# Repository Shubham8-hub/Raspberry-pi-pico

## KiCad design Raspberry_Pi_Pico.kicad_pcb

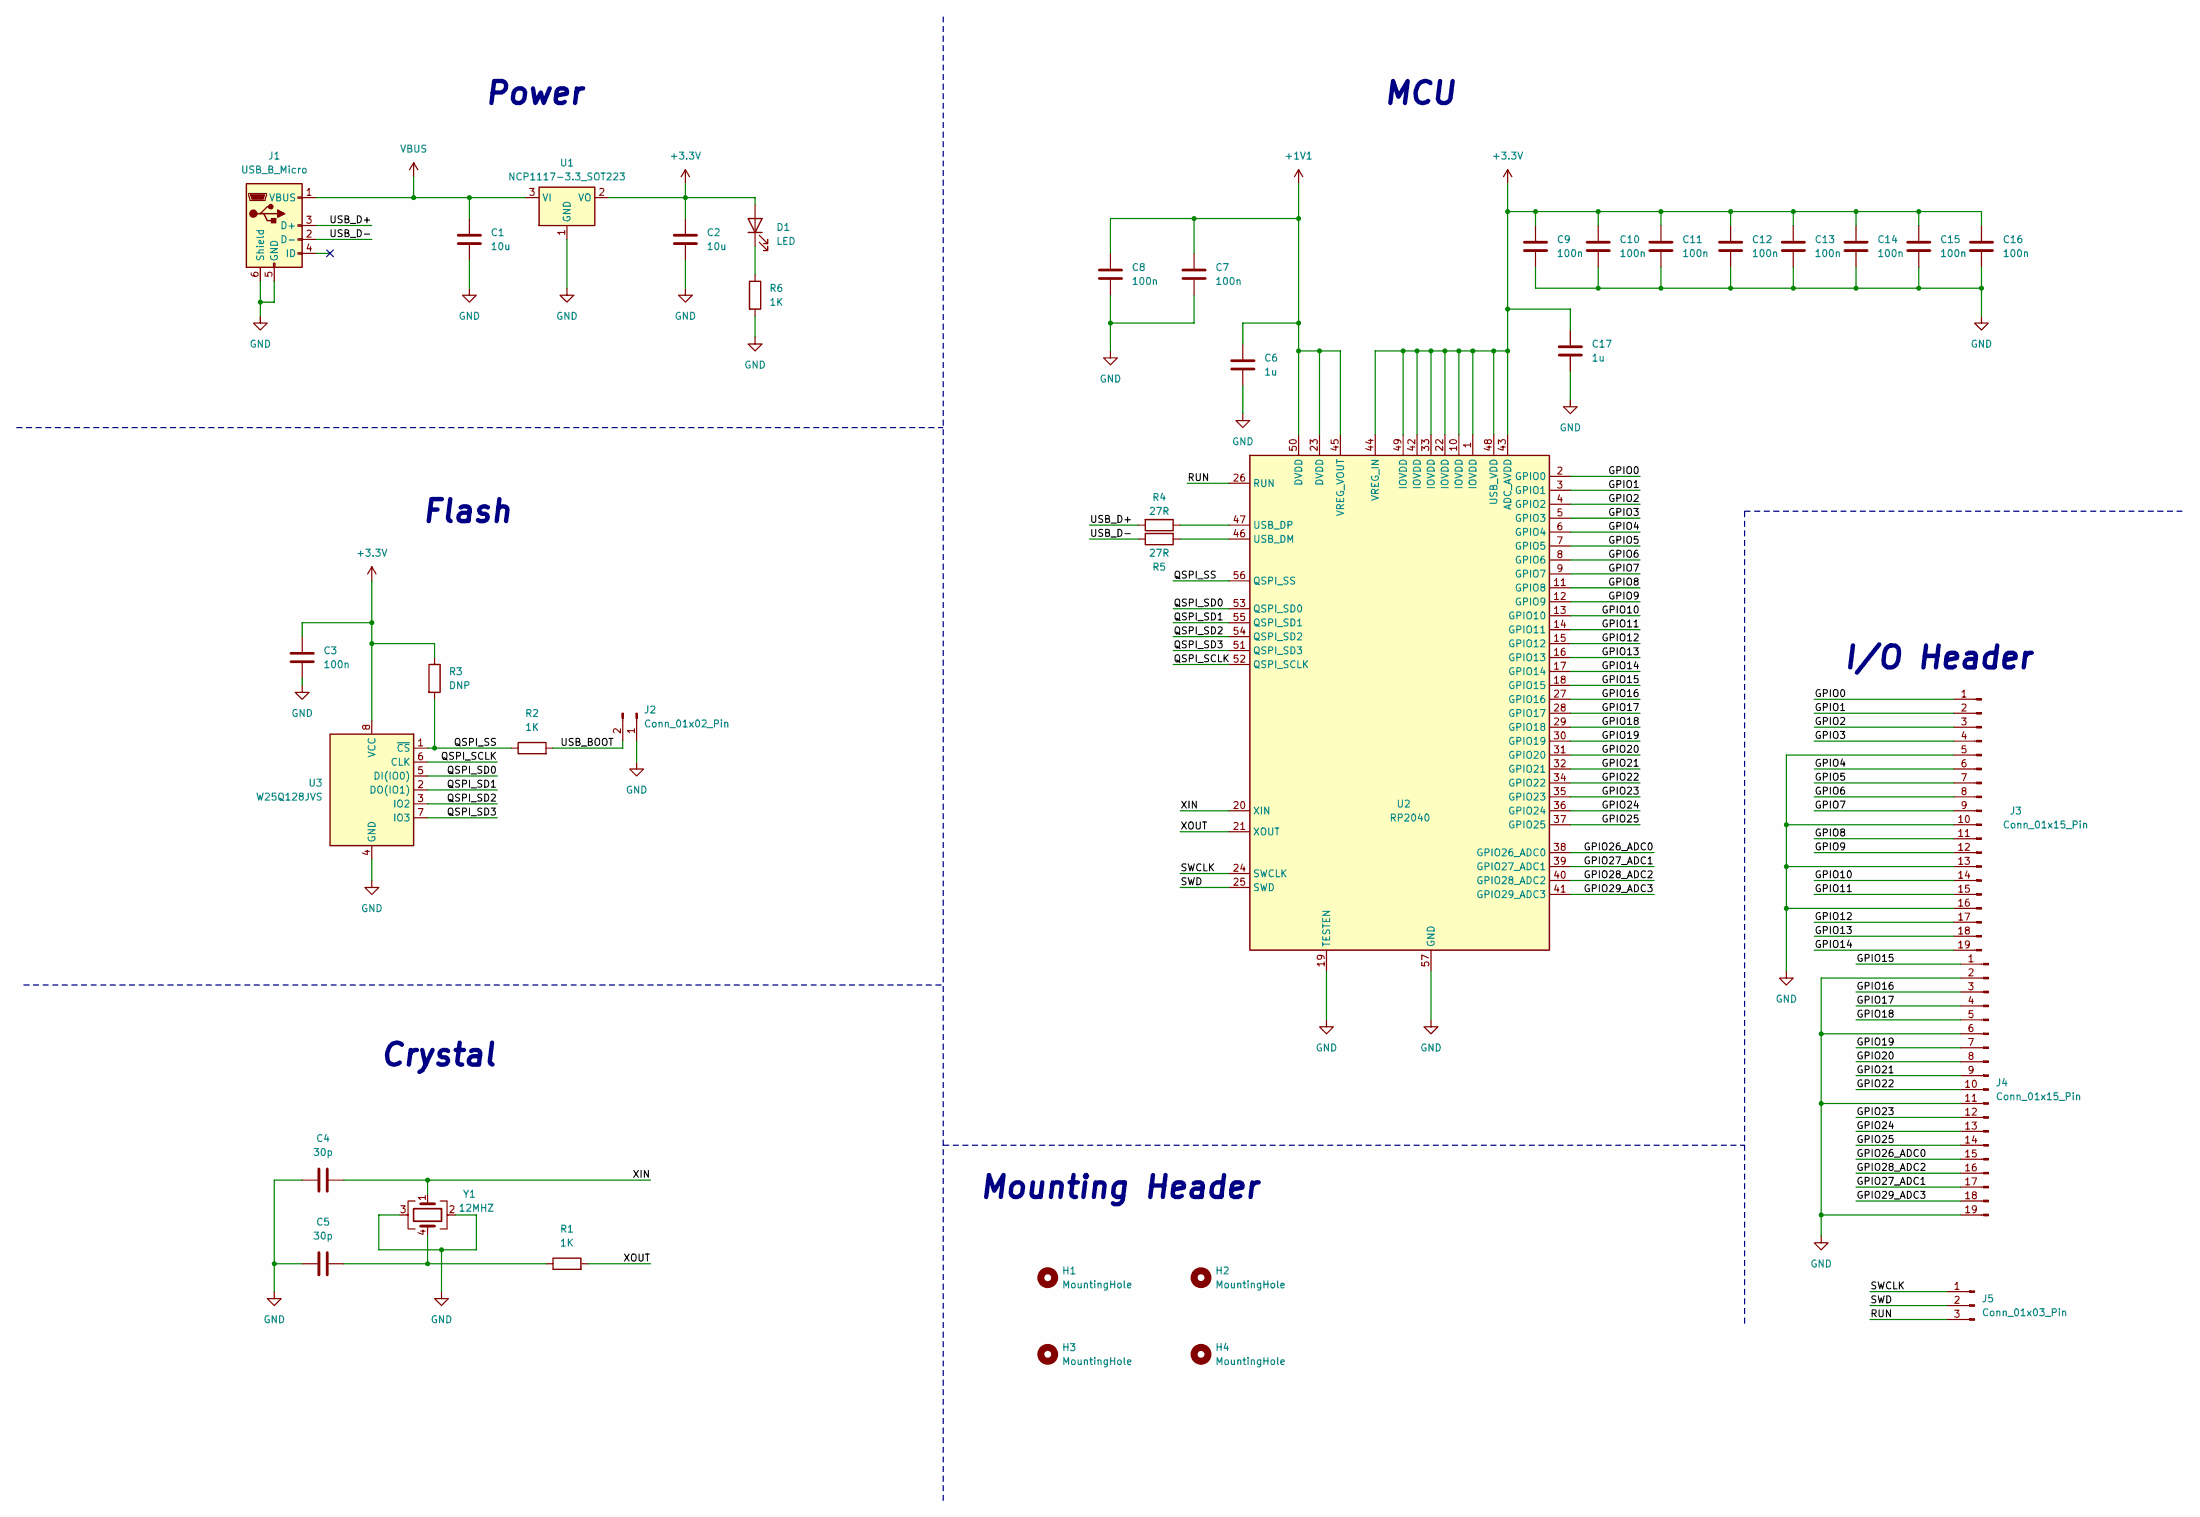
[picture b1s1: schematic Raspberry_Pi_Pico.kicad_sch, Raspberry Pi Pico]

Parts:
C1, C2: 10u; C_0805_2012Metric_Pad1.18x1.45mm_HandSolder
C3, C7, C8, C9, C10, C11, C12, C13, C14, C15, C16: 100n; C_0805_2012Metric_Pad1.18x1.45mm_HandSolder
C4, C5: 30p; C_0805_2012Metric_Pad1.18x1.45mm_HandSolder
C6, C17: 1u; C_0805_2012Metric_Pad1.18x1.45mm_HandSolder
D1: LED; LED_0805_2012Metric
H1, H2, H3, H4: MountingHole; MountingHole_3.2mm_M3_DIN965
J1: USB_B_Micro; USB_Micro-B_Wuerth_629105150521_CircularHoles
J2: Conn_01x02_Pin; PinHeader_1x02_P2.54mm_Vertical
J3, J4: Conn_01x15_Pin; PinHeader_1x19_P2.54mm_Vertical
J5: Conn_01x03_Pin; PinHeader_1x03_P2.54mm_Vertical
R1, R2, R6: 1K; R_0805_2012Metric_Pad1.20x1.40mm_HandSolder
R3: DNP; R_0805_2012Metric_Pad1.20x1.40mm_HandSolder
R4, R5: 27R; R_0805_2012Metric_Pad1.20x1.40mm_HandSolder
U1: NCP1117-3.3_SOT223; SOT-223-3_TabPin2
U2: RP2040; QFN-56-1EP_7x7mm_P0.4mm_EP3.2x3.2mm
U3: W25Q128JVS; SOIC-8_5.23x5.23mm_P1.27mm
Y1: 12MHZ; Crystal_SMD_7050-4Pin_7.0x5.0mm

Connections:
+1V1: C6.1, C7.1, C8.1, U2.23 (DVDD), U2.45 (VREG_VOUT), U2.50 (DVDD)
+3.3V: C2.1, C3.1, C9.1, C10.1, C11.1, C12.1, C13.1, C14.1, C15.1, C16.1, C17.1, D1.2 (A), R3.1, U1.2 (VO), U2.1 (IOVDD), U2.10 (IOVDD), U2.22 (IOVDD), U2.33 (IOVDD), U2.42 (IOVDD), U2.43 (ADC_AVDD), U2.44 (VREG_IN), U2.48 (USB_VDD), U2.49 (IOVDD), U3.8 (VCC)
/GPIO0: J3.1, U2.2 (GPIO0)
/GPIO1: J3.2, U2.3 (GPIO1)
/GPIO2: J3.3, U2.4 (GPIO2)
/GPIO3: J3.4, U2.5 (GPIO3)
/GPIO4: J3.6, U2.6 (GPIO4)
/GPIO5: J3.7, U2.7 (GPIO5)
/GPIO6: J3.8, U2.8 (GPIO6)
/GPIO7: J3.9, U2.9 (GPIO7)
/GPIO8: J3.11, U2.11 (GPIO8)
/GPIO9: J3.12, U2.12 (GPIO9)
/GPIO10: J3.14, U2.13 (GPIO10)
/GPIO11: J3.15, U2.14 (GPIO11)
/GPIO12: J3.17, U2.15 (GPIO12)
/GPIO13: J3.18, U2.16 (GPIO13)
/GPIO14: J3.19, U2.17 (GPIO14)
/GPIO15: J4.1, U2.18 (GPIO15)
/GPIO16: J4.3, U2.27 (GPIO16)
/GPIO17: J4.4, U2.28 (GPIO17)
/GPIO18: J4.5, U2.29 (GPIO18)
/GPIO19: J4.7, U2.30 (GPIO19)
/GPIO20: J4.8, U2.31 (GPIO20)
/GPIO21: J4.9, U2.32 (GPIO21)
/GPIO22: J4.10, U2.34 (GPIO22)
/GPIO23: J4.12, U2.35 (GPIO23)
/GPIO24: J4.13, U2.36 (GPIO24)
/GPIO25: J4.14, U2.37 (GPIO25)
/GPIO26_ADC0: J4.15, U2.38 (GPIO26_ADC0)
/GPIO27_ADC1: J4.17, U2.39 (GPIO27_ADC1)
/GPIO28_ADC2: J4.16, U2.40 (GPIO28_ADC2)
/GPIO29_ADC3: J4.18, U2.41 (GPIO29_ADC3)
/QSPI_SCLK: U2.52 (QSPI_SCLK), U3.6 (CLK)
/QSPI_SD0: U2.53 (QSPI_SD0), U3.5 (DI(IO0))
/QSPI_SD1: U2.55 (QSPI_SD1), U3.2 (DO(IO1))
/QSPI_SD2: U2.54 (QSPI_SD2), U3.3 (IO2)
/QSPI_SD3: U2.51 (QSPI_SD3), U3.7 (IO3)
/QSPI_SS: R2.1, R3.2, U2.56 (QSPI_SS), U3.1 (~CS)
/RUN: J5.3, U2.26 (RUN)
/SWCLK: J5.1, U2.24 (SWCLK)
/SWD: J5.2, U2.25 (SWD)
/USB_BOOT: J2.2, R2.2
/USB_D+: J1.3 (D+), R4.2
/USB_D-: J1.2 (D-), R5.1
/XIN: C4.2, U2.20 (XIN), Y1.1
/XOUT: R1.2, U2.21 (XOUT)
GND: C1.2, C2.2, C3.2, C4.1, C5.1, C6.2, C7.2, C8.2, C9.2, C10.2, C11.2, C12.2, C13.2, C14.2, C15.2, C16.2, C17.2, J1.5 (GND), J1.6 (Shield), J2.1, J3.5, J3.10, J3.13, J3.16, J4.2, J4.6, J4.11, J4.19, R6.2, U1.1 (GND), U2.19 (TESTEN), U2.57 (GND), U3.4 (GND), Y1.2, Y1.3
unnamed: C5.2, R1.1, Y1.4
unnamed: D1.1 (K), R6.1
unnamed: R5.2, U2.46 (USB_DM)
unnamed: R4.1, U2.47 (USB_DP)
VBUS: C1.1, J1.1 (VBUS), U1.3 (VI)

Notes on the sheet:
Crystal
MCU
I/O Header
Power
Flash
Mounting Header

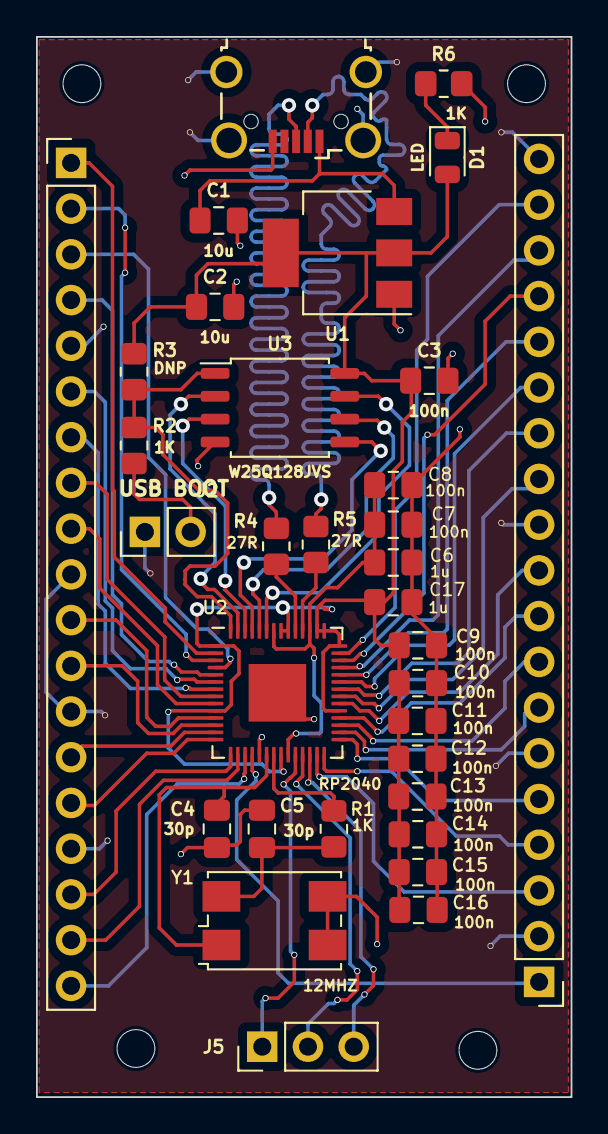
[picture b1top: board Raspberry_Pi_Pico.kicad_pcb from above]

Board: 4 copper layers, 29.7 x 58.9 mm, 37 parts (0 on the bottom side), 52 nets.
